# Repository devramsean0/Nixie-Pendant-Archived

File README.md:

A DIY, wearable pendant made from an IN-16 and quite a few boards

> [!CAUTION]
> This project contains high voltage electronics, It could concevably kill you and it will hurt.
> Don't leave children unnatended and exercise caution

## Key Voltages
LV: 3.3v, HV: 170v

## Planned electrical stackup
This is in order of closest to tube
1. Socket PCB
2. Control PCB
3. High Voltage Generation PCB
4. BMS board
5. Programming/Charging board
6. Battery

## Folder Layout
- `bms/` - Board files for the BMS (Battery Management System), handles lipo charging and safe discharge, usb & battery cutover and power regulation to the LV rail
- `socket/` - My bootleg IN-16 socket, very simple. just pads and holes. but like, this should hold the tube in (probably)
- `PendantLib.pretty/` - Shared part footprints

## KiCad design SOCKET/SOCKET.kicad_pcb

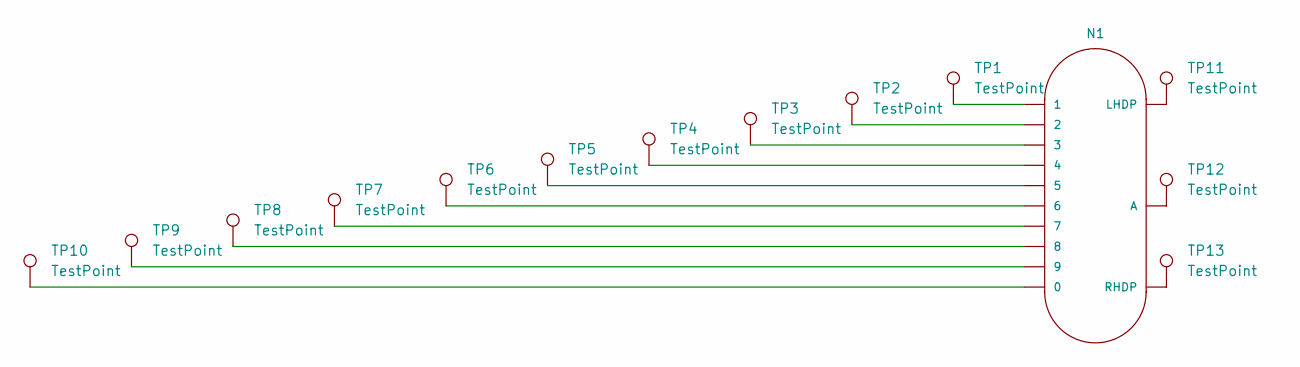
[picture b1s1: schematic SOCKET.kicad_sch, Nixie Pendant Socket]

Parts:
N1: IN-16; nixies-us-IN-16
TP1, TP2, TP3, TP4, TP5, TP6, TP7, TP8, TP9, TP10, TP11, TP12, TP13: TestPoint; TestPoint_Pad_1.0x1.0mm

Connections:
unnamed: N1.0, TP10.1
unnamed: N1.1, TP1.1
unnamed: N1.2, TP2.1
unnamed: N1.3, TP3.1
unnamed: N1.4, TP4.1
unnamed: N1.5, TP5.1
unnamed: N1.6, TP6.1
unnamed: N1.7, TP7.1
unnamed: N1.8, TP8.1
unnamed: N1.9, TP9.1
unnamed: N1.A, TP12.1
unnamed: N1.LHDP, TP11.1
unnamed: N1.RHDP, TP13.1

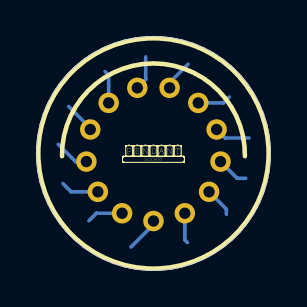
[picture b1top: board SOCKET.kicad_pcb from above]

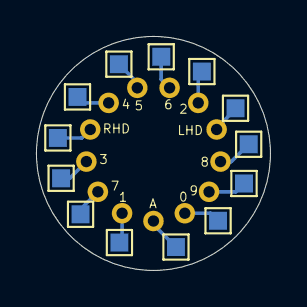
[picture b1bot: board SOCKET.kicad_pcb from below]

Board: 2 copper layers, 13.0 x 13.0 mm, 14 parts (13 on the bottom side), 13 nets.

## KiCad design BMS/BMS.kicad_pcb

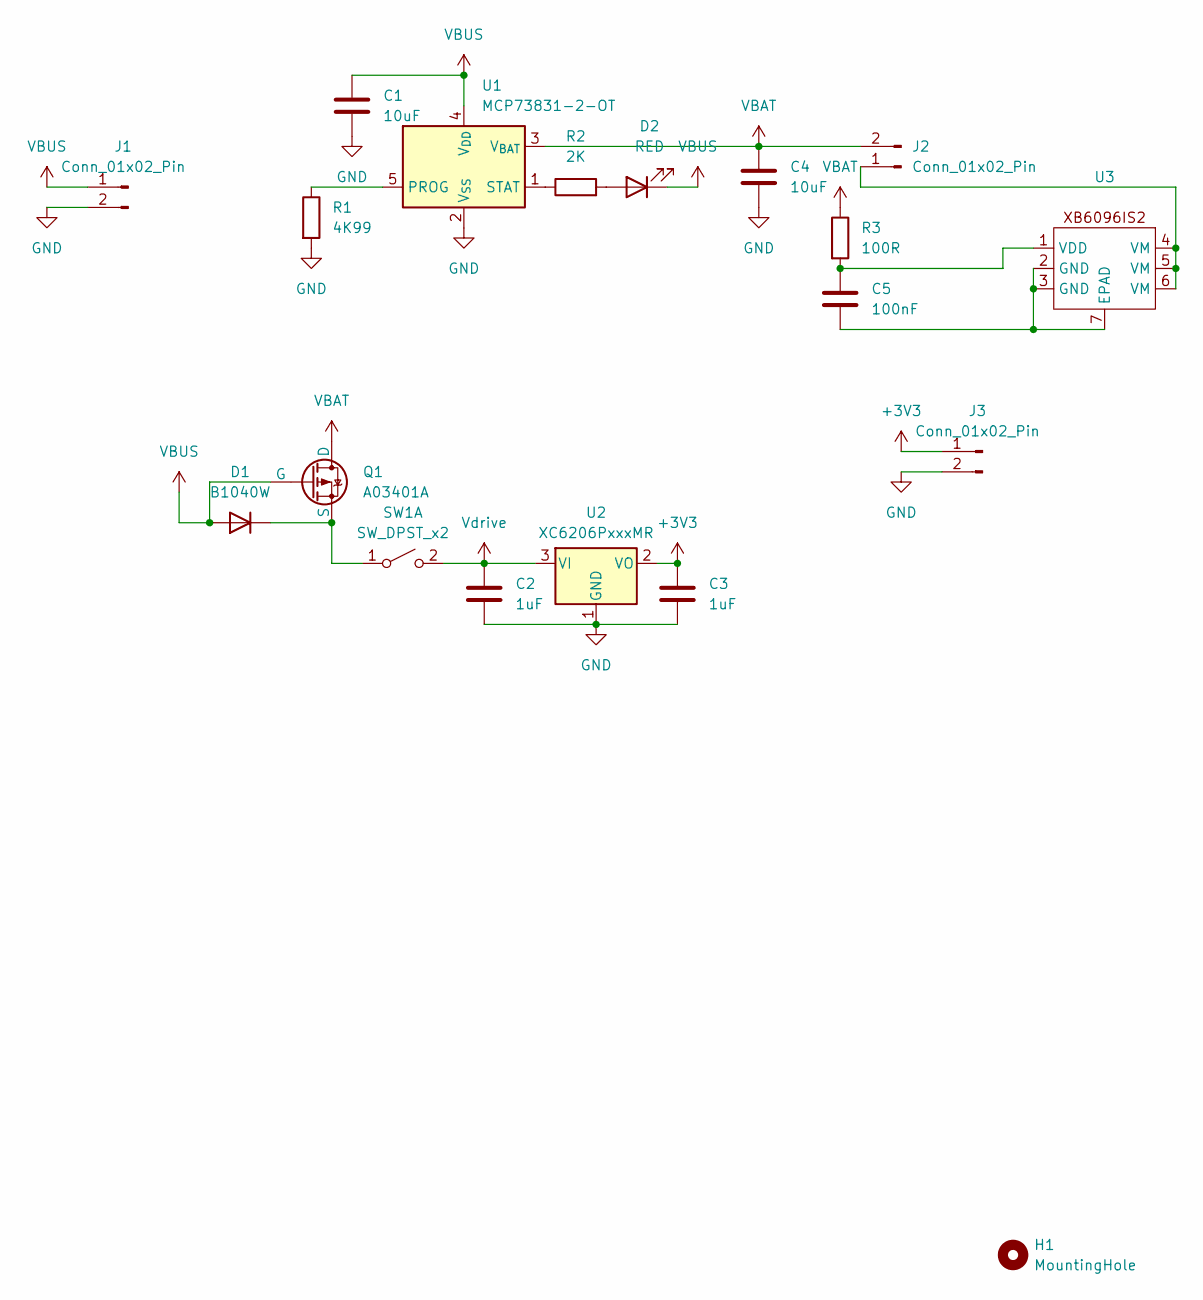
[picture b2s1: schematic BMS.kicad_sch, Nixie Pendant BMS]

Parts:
C1, C4: 10uF; C_0402_1005Metric
C2, C3: 1uF; C_0402_1005Metric
C5: 100nF; C_0402_1005Metric
D1: B1040W; D_SOD-123
D2: RED; LED_0603_1608Metric
H1: MountingHole; MountingHole_1.5mm
J1, J2, J3: Conn_01x02_Pin; PinHeader_2x01_P1.00mm_Vertical
Q1: A03401A; TSOT-23
R1: 4K99; R_0402_1005Metric
R2: 2K; R_0402_1005Metric
R3: 100R; R_0402_1005Metric
SW1: SW_DPST_x2; PinHeader_2x01_P1.00mm_Vertical
U1: MCP73831-2-OT; SOT-23-5
U2: XC6206PxxxMR; SOT-23-3
U3: DFN-6-1EP_2x2mm_P0.5mm_EP0.6x1.37mm

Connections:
+3V3: C3.1, J3.1, U2.2 (VO)
GND: C1.2, C2.2, C3.2, C4.2, J1.2, J3.2, R1.2, U1.2 (V_{SS}), U2.1 (GND)
unnamed: D1.1 (K), Q1.3 (S), SW1.1 (A)
unnamed: D2.2 (A), R2.2
unnamed: J2.1, U3.4 (VM), U3.5 (VM), U3.6 (VM)
unnamed: R1.1, U1.5 (PROG)
unnamed: R2.1, U1.1 (STAT)
unnamed: C5.2, U3.2 (GND), U3.3 (GND), U3.7 (EPAD)
unnamed: C5.1, R3.2, U3.1 (VDD)
VBAT: C4.1, J2.2, Q1.1 (D), R3.1, U1.3 (V_{BAT})
VBUS: C1.1, D1.2 (A), D2.1 (K), J1.1, Q1.2 (G), U1.4 (V_{DD})
Vdrive: C2.1, SW1.2 (B), U2.3 (VI)

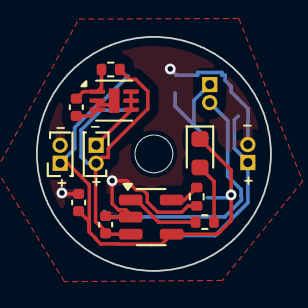
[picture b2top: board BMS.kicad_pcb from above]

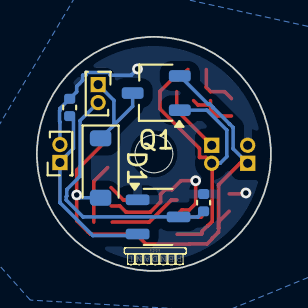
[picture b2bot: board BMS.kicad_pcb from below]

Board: 2 copper layers, 13.0 x 13.0 mm, 19 parts (7 on the bottom side), 12 nets.

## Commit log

2024-12-21 BMS Board
2025-01-05 BMS Rev 2
2025-01-06 BMS rev 3, Shared lib, WIP blog, A readme
2025-01-06 Some BMS changes?, Socket PCB
